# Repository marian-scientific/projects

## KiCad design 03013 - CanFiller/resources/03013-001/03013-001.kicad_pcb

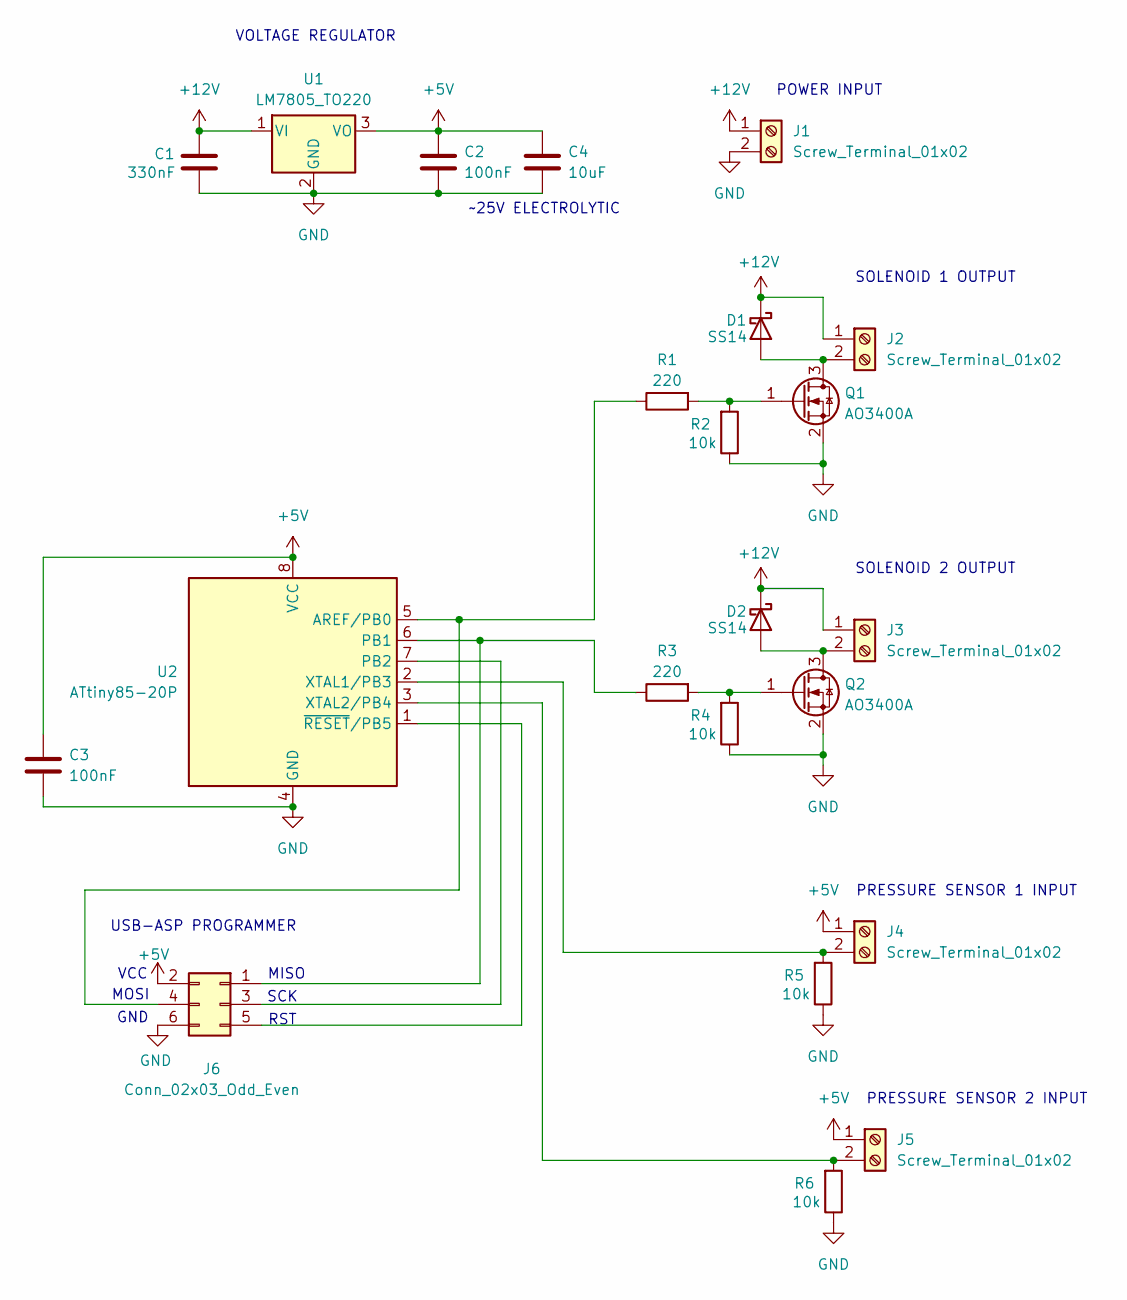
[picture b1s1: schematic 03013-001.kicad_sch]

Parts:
C1: 330nF; C_1206_3216Metric
C2, C3: 100nF; C_1206_3216Metric
C4: 10uF; CP_Radial_D5.0mm_P2.50mm
D1, D2: SS14; D_SMA
J1, J2, J3, J4, J5: Screw_Terminal_01x02; TerminalBlock_Phoenix_MKDS-1,5-2-5.08_1x02_P5.08mm_Horizont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
J6: Conn_02x03_Odd_Even; PinHeader_2x03_P2.54mm_Vertical
Q1, Q2: AO3400A; SOT-23
R1, R3: 220; R_1206_3216Metric
R2, R4, R5, R6: 10k; R_1206_3216Metric
U1: LM7805_TO220; TO-220-3_Vertical
U2: ATtiny85-20P; DIP-8_W7.62mm

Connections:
+5V: C2.1, C3.1, C4.1, J4.1, J5.1, J6.2, U1.3 (VO), U2.8 (VCC)
+12V: C1.1, D1.1 (K), D2.1 (K), J1.1, J2.1, J3.1, U1.1 (VI)
GND: C1.2, C2.2, C3.2, C4.2, J1.2, J6.6, Q1.2 (S), Q2.2 (S), R2.1, R4.1, R5.1, R6.1, U1.2 (GND), U2.4 (GND)
unnamed: D1.2 (A), J2.2, Q1.3 (D)
unnamed: D2.2 (A), J3.2, Q2.3 (D)
unnamed: J4.2, R5.2, U2.2 (XTAL1/PB3)
unnamed: J5.2, R6.2, U2.3 (XTAL2/PB4)
unnamed: J6.1, R3.1, U2.6 (PB1)
unnamed: J6.3, U2.7 (PB2)
unnamed: J6.4, R1.1, U2.5 (AREF/PB0)
unnamed: J6.5, U2.1 (~RESET/PB5)
unnamed: Q1.1 (G), R1.2, R2.2
unnamed: Q2.1 (G), R3.2, R4.2

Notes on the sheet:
GND
SOLENOID 1 OUTPUT
PRESSURE SENSOR 1 INPUT
VOLTAGE REGULATOR
MOSI
VCC
MISO
~25V ELECTROLYTIC
USB-ASP PROGRAMMER
POWER INPUT
PRESSURE SENSOR 2 INPUT
RST
SOLENOID 2 OUTPUT
SCK

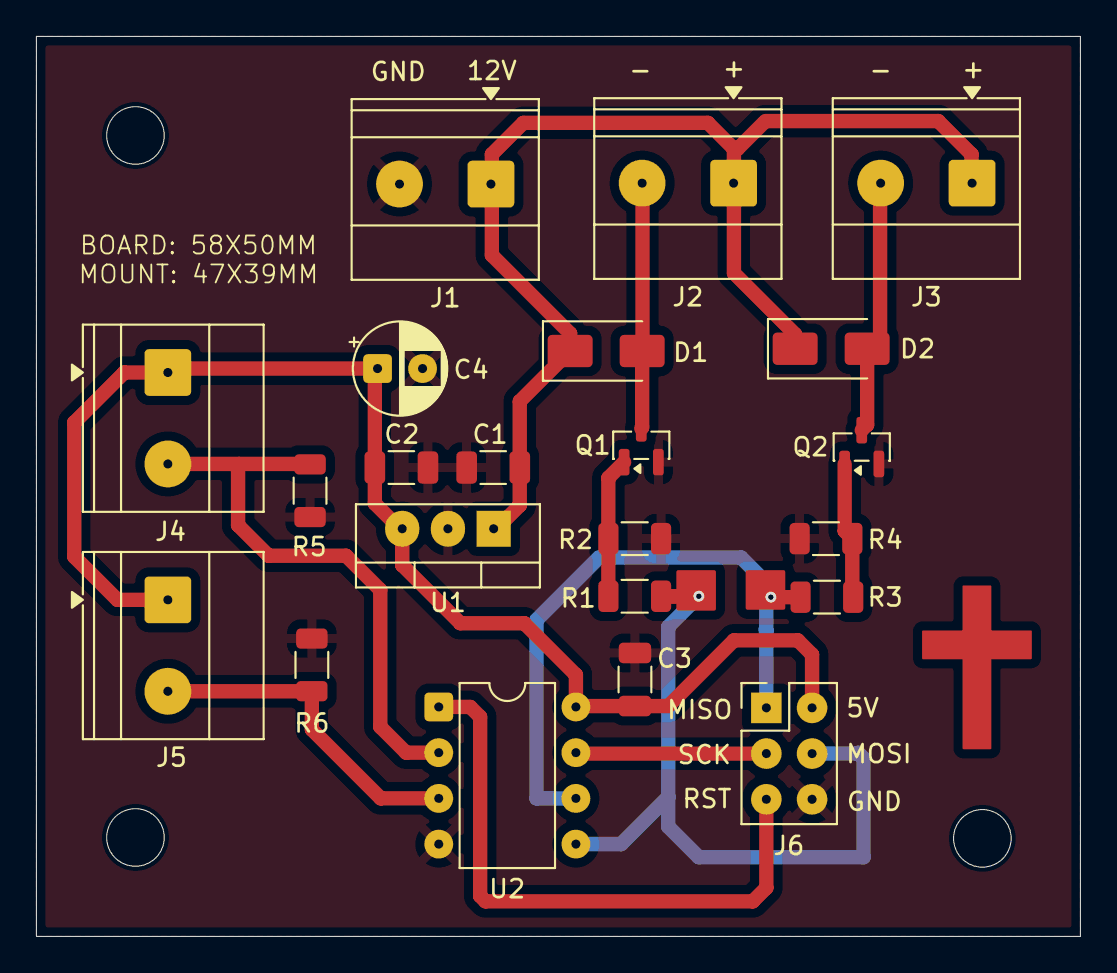
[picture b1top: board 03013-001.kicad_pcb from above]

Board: 2 copper layers, 58.0 x 50.0 mm, 22 parts (0 on the bottom side), 13 nets.

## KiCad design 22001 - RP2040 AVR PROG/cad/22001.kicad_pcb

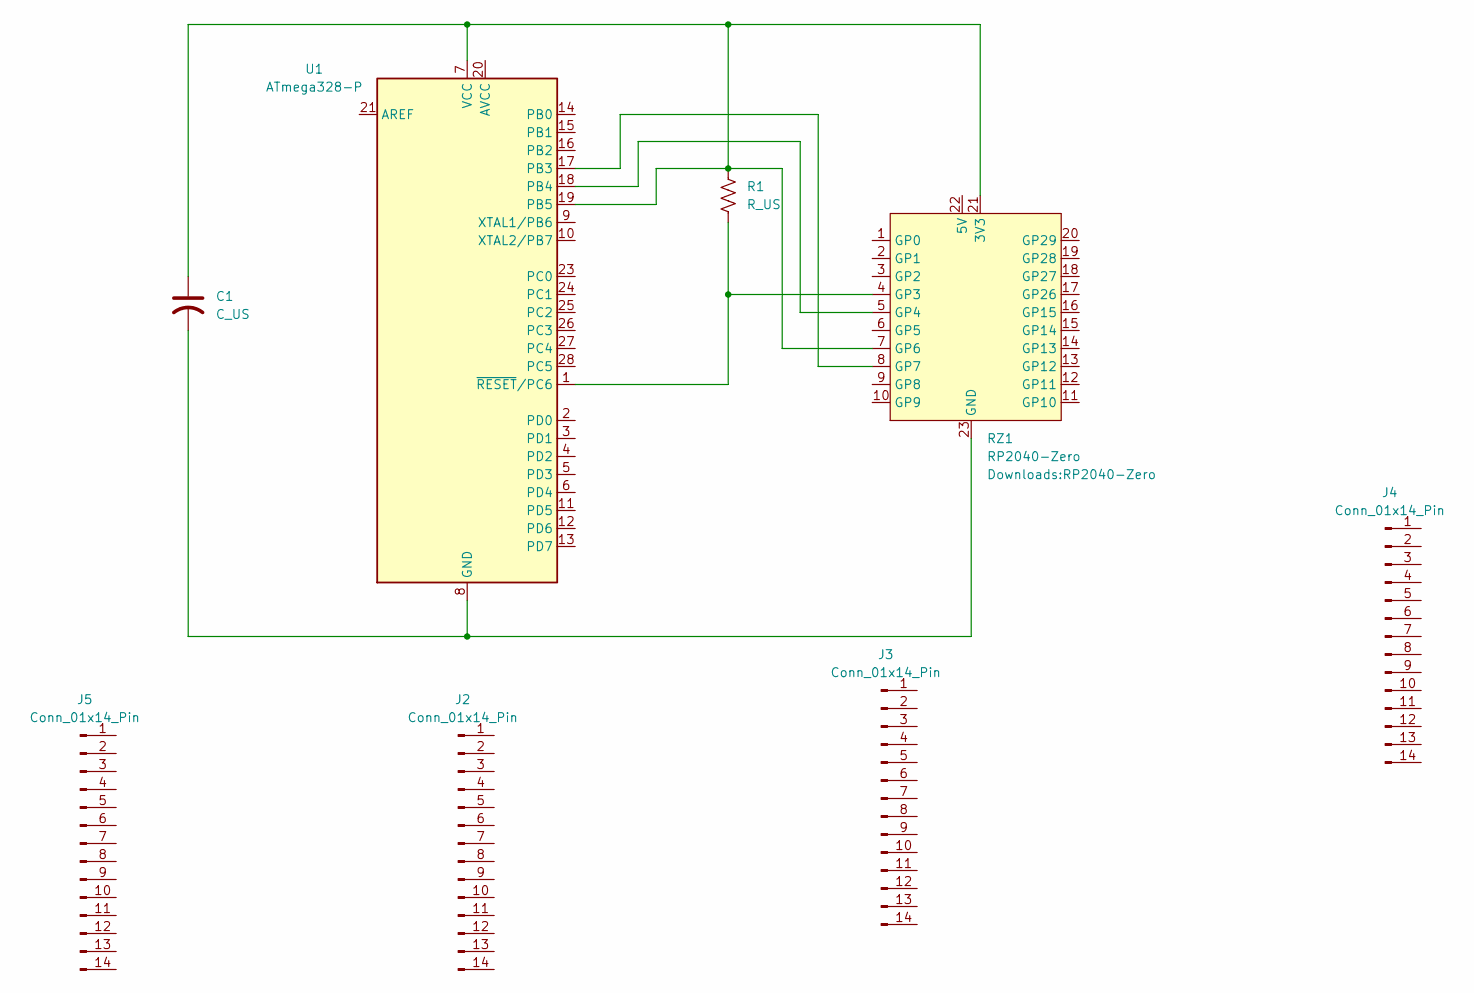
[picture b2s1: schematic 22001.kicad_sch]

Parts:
C1: C_US; C_Disc_D5.0mm_W2.5mm_P5.00mm
J2, J3, J4, J5: Conn_01x14_Pin; PinHeader_1x14_P2.54mm_Vertical
R1: R_US; R_Axial_DIN0207_L6.3mm_D2.5mm_P10.16mm_Horizontal
RZ1: RP2040-Zero
U1: ATmega328-P; DIP-28_W7.62mm

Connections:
unnamed: C1.1, R1.1, RZ1.7 (GP6), RZ1.21 (3V3), U1.7 (VCC), U1.19 (PB5)
unnamed: C1.2, RZ1.23 (GND), U1.8 (GND), U1.22 (GND)
unnamed: R1.2, RZ1.4 (GP3), U1.1 (~RESET/PC6)
unnamed: RZ1.5 (GP4), U1.18 (PB4)
unnamed: RZ1.8 (GP7), U1.17 (PB3)

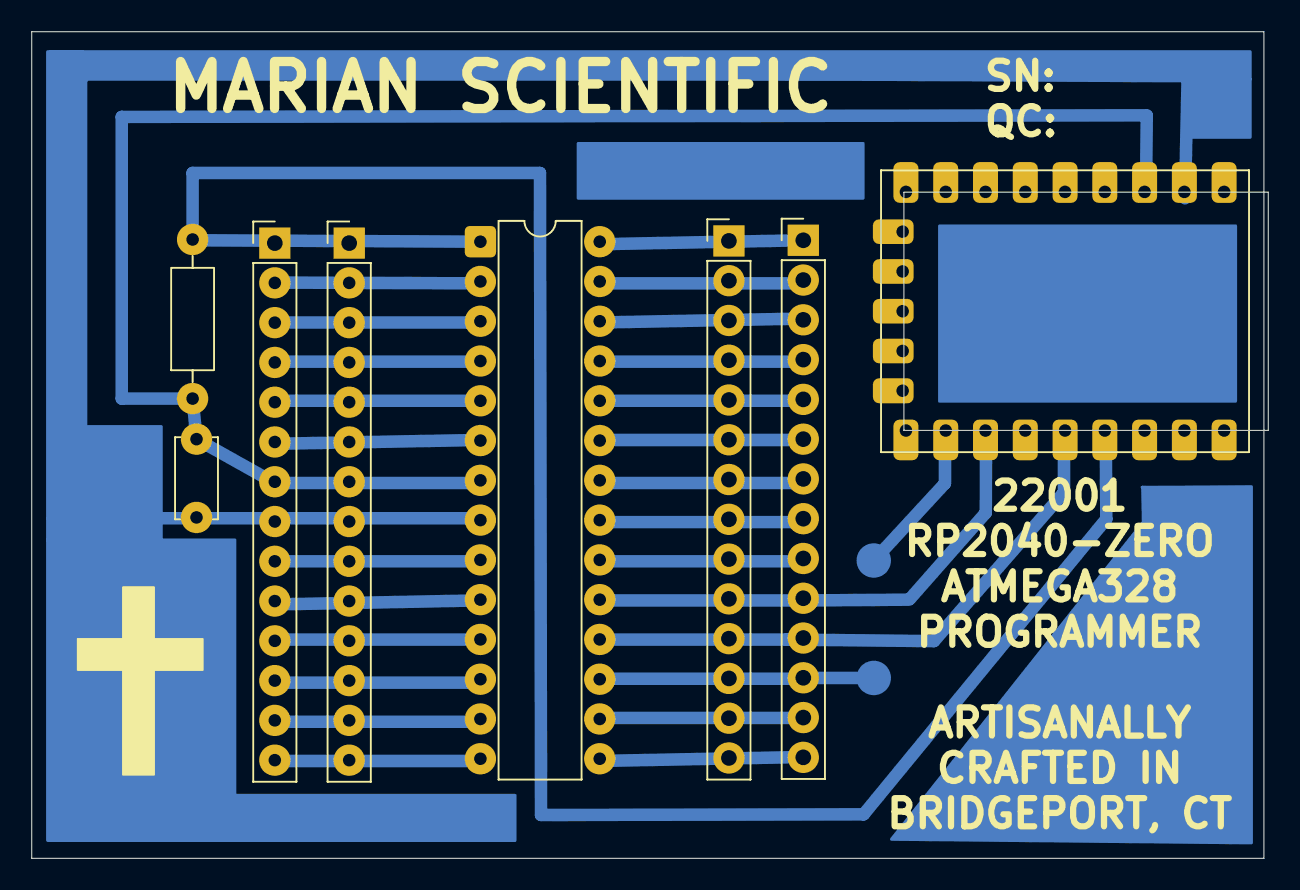
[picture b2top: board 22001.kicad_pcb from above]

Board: 2 copper layers, 78.7 x 52.8 mm, 8 parts (0 on the bottom side), 5 nets.

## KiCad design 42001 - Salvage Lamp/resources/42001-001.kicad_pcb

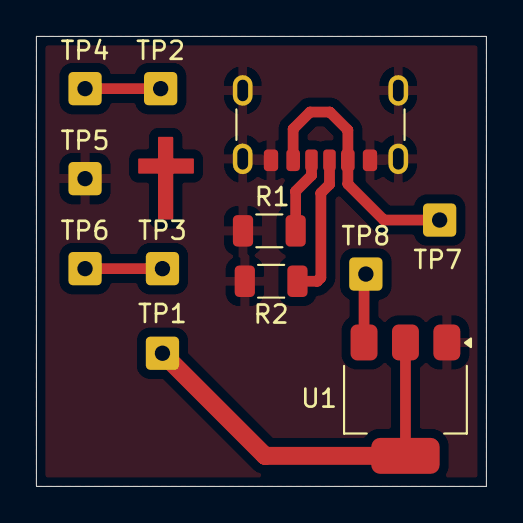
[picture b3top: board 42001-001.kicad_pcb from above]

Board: 2 copper layers, 25.0 x 25.0 mm, 12 parts (0 on the bottom side), 8 nets.

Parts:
J1: USB_C_Receptacle_PowerOnly_6P; USB_C_Receptacle_GCT_USB4125-xx-x_6P_TopMnt_Horizontal
R1, R2: 5.1k; R_1206_3216Metric
TP1: Lamp Red; SolderWire-0.25sqmm_1x01_D0.65mm_OD1.7mm
TP2: Lamp Black; SolderWire-0.25sqmm_1x01_D0.65mm_OD1.7mm
TP3: Lamp Yellow; SolderWire-0.25sqmm_1x01_D0.65mm_OD1.7mm
TP4, TP7: Switch 1; SolderWire-0.25sqmm_1x01_D0.65mm_OD1.7mm
TP5, TP8: Switch 2; SolderWire-0.25sqmm_1x01_D0.65mm_OD1.7mm
TP6: Switch 3; SolderWire-0.25sqmm_1x01_D0.65mm_OD1.7mm
U1: AMS1117-3.3; SOT-223-3_TabPin2

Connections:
GND: J1.A12 (GND), J1.B12 (GND), J1.S1 (SHIELD), R1.2, R2.2, TP5.1, U1.1 (GND)
unnamed: J1.A5 (CC1), R2.1
unnamed: J1.B5 (CC2), R1.1
unnamed: TP2.1, TP4.1
unnamed: TP3.1, TP6.1
unnamed: J1.A9 (VBUS), J1.B9 (VBUS), TP7.1
unnamed: TP8.1, U1.3 (VI)
unnamed: TP1.1, U1.2 (VO)
